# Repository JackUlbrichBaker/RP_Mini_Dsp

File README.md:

# DSP board

TODO:
- [ ] Create catchy name
- [x] Complete schematics
- [ ] review schematics
- [ ] revise schematics (if needed)
- [ ] Route board
- [ ] layout board

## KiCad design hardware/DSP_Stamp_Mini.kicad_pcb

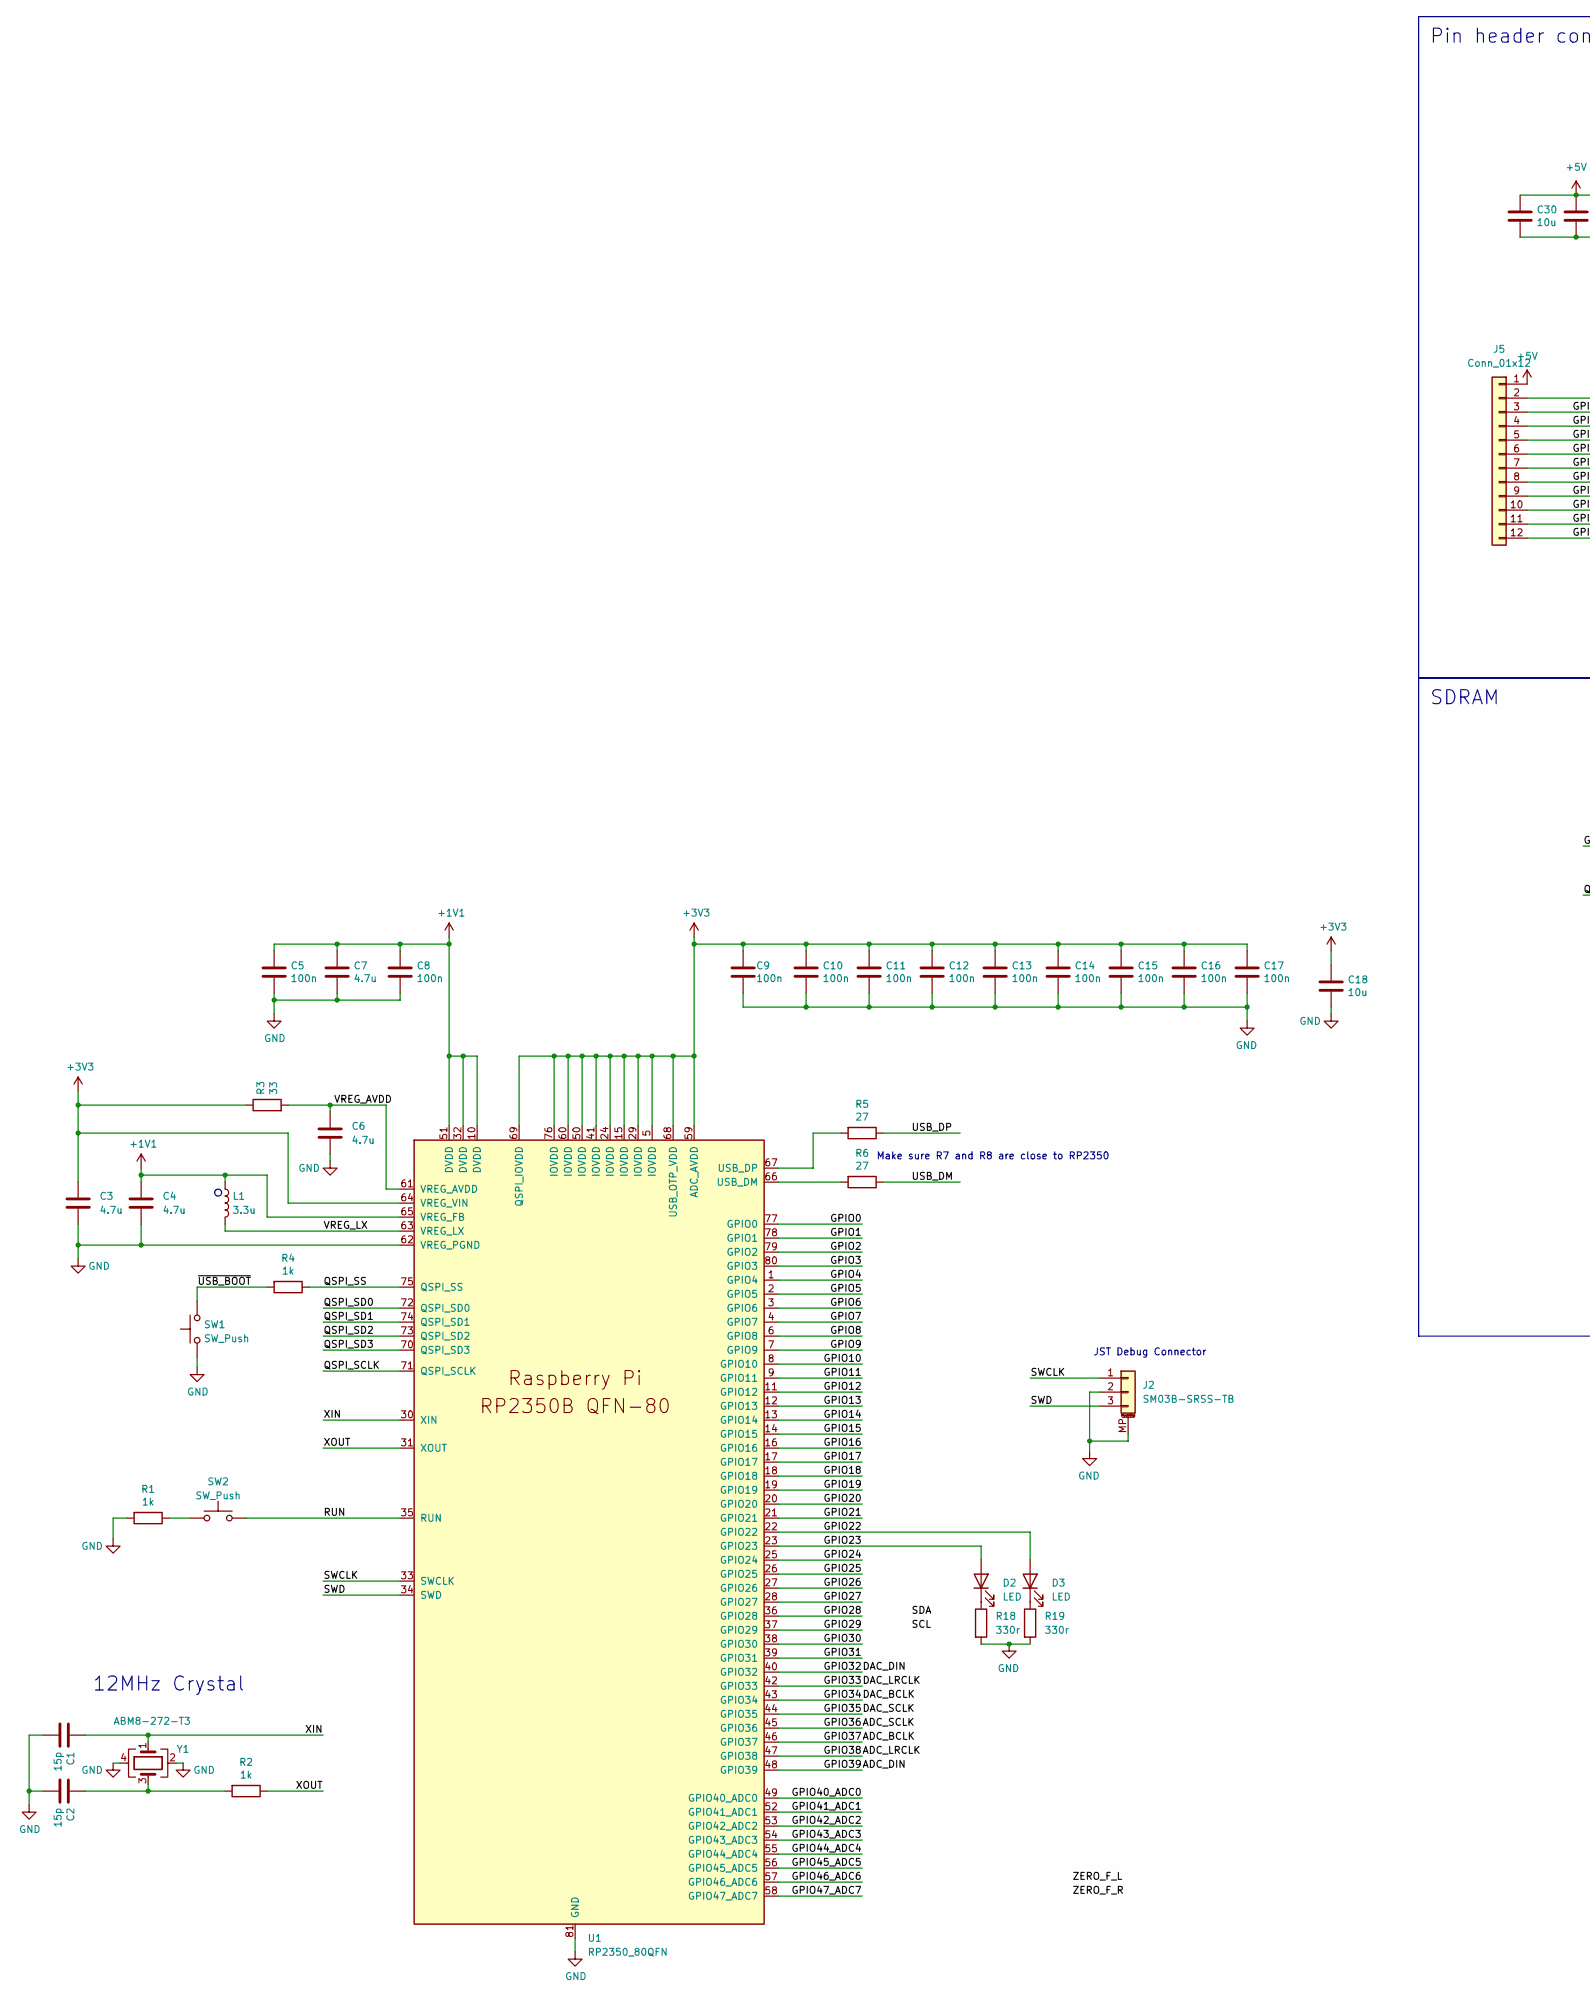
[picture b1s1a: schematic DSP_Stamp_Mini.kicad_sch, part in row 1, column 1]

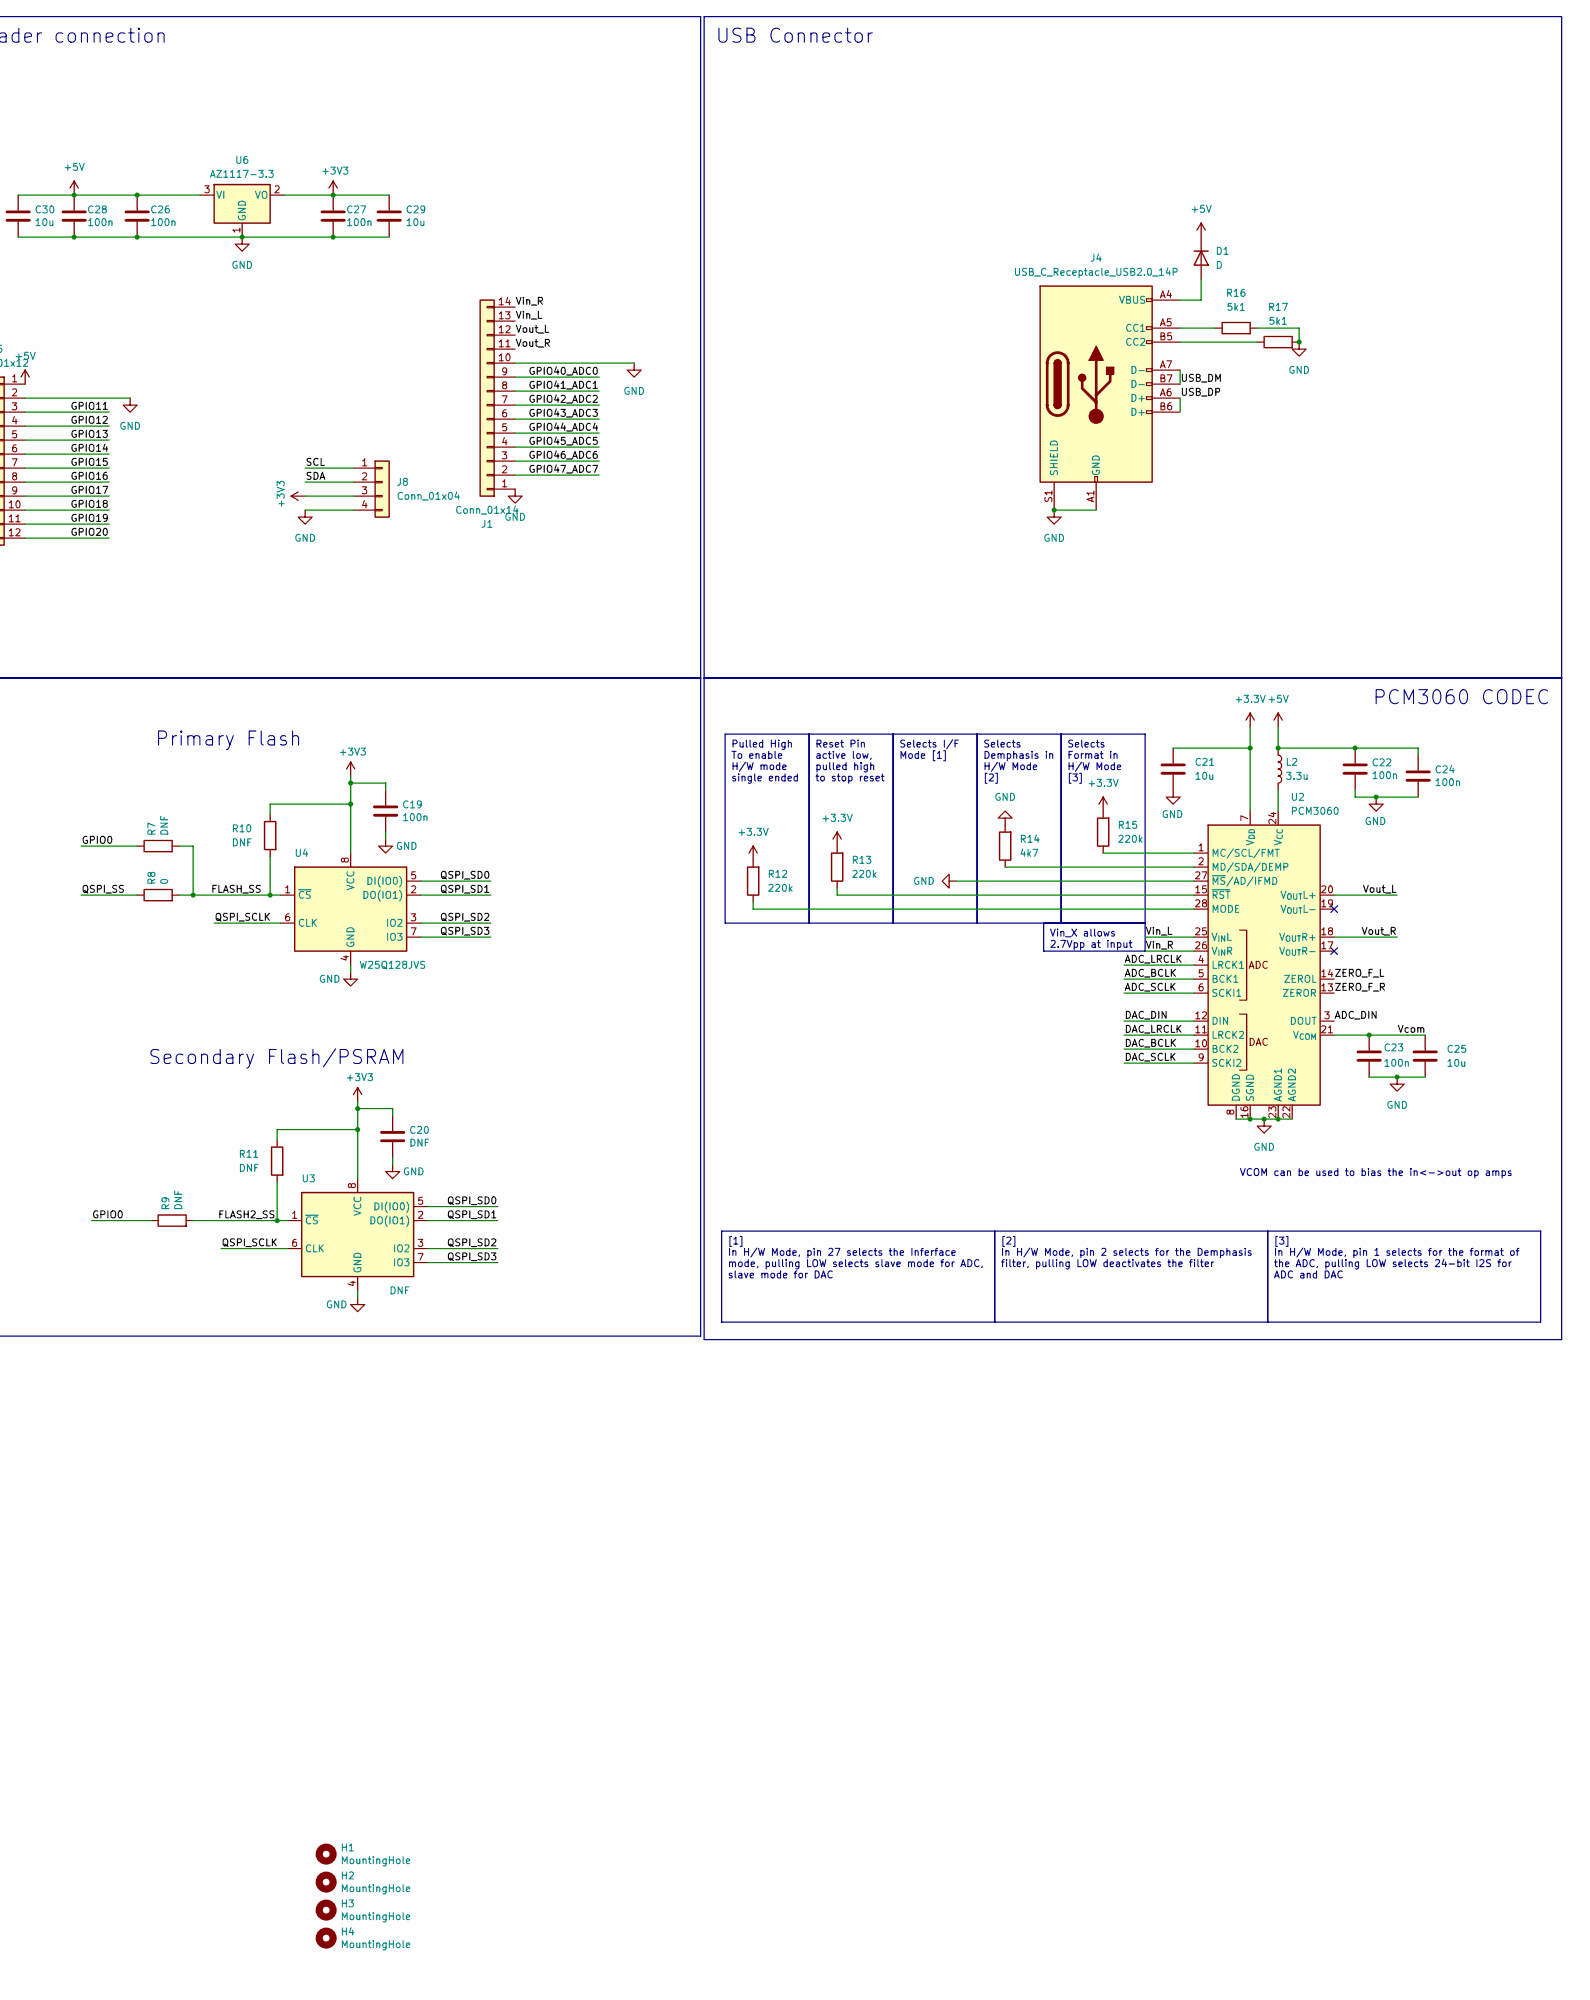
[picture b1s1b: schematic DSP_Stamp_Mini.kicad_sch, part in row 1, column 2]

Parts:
C1, C2: 15p; C_0603_1608Metric_Pad1.08x0.95mm_HandSolder
C3, C4, C6, C7: 4.7u; C_0603_1608Metric_Pad1.08x0.95mm_HandSolder
C5, C8, C9, C10, C11, C12, C13, C14, C15, C16, C17, C19, C22, C23, C24, C26, C27, C28: 100n; C_0603_1608Metric_Pad1.08x0.95mm_HandSolder
C18, C21, C25, C29, C30: 10u; C_0603_1608Metric_Pad1.08x0.95mm_HandSolder
C20: DNF; C_0603_1608Metric_Pad1.08x0.95mm_HandSolder
D1: D; D_0603_1608Metric
D2, D3: LED; LED_0603_1608Metric_Pad1.05x0.95mm_HandSolder
H1, H2, H3, H4: MountingHole; MountingHole_2.7mm_M2.5
J1: Conn_01x14; PinHeader_1x14_P2.54mm_Vertical
J2: SM03B-SRSS-TB; JST_SH_SM03B-SRSS-TB_1x03-1MP_P1.00mm_Horizontal
J4: USB_C_Receptacle_USB2.0_14P; USB_C_Receptacle_GCT_USB4105-xx-A_16P_TopMnt_Horizontal
J5: Conn_01x12; PinHeader_1x12_P2.54mm_Vertical
J8: Conn_01x04; JST_SH_SM04B-SRSS-TB_1x04-1MP_P1.00mm_Horizontal; Part Number 1-0401FBV0T
L1, L2: 3.3u; L_pol_2016
R1, R2, R4: 1k; R_0603_1608Metric_Pad0.98x0.95mm_HandSolder
R3: 33; R_0603_1608Metric_Pad0.98x0.95mm_HandSolder
R5, R6: 27; R_0603_1608Metric_Pad0.98x0.95mm_HandSolder
R7, R9, R10, R11: DNF; R_0603_1608Metric_Pad0.98x0.95mm_HandSolder
R8: 0; R_0603_1608Metric_Pad0.98x0.95mm_HandSolder
R12, R13, R15: 220k; R_0603_1608Metric_Pad0.98x0.95mm_HandSolder
R14: 4k7; R_0603_1608Metric_Pad0.98x0.95mm_HandSolder
R16, R17: 5k1; R_0603_1608Metric_Pad0.98x0.95mm_HandSolder
R18, R19: 330r; R_0603_1608Metric_Pad0.98x0.95mm_HandSolder
SW1, SW2: SW_Push; SW_Push_1P1T_NO_Vertical_Wuerth_434133025816
U1: RP2350_80QFN; RP2350-QFN-80-1EP_10x10_P0.4mm_EP3.4x3.4mm_ThermalVias
U2: PCM3060; TSSOP-28_4.4x9.7mm_P0.65mm
U3: DNF; SOIC-8_5.23x5.23mm_P1.27mm
U4: W25Q128JVS; SOIC-8_5.23x5.23mm_P1.27mm
U6: AZ1117-3.3; SOT-89-3
Y1: ABM8-272-T3; Crystal_SMD_3225-4Pin_3.2x2.5mm

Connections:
+1V1: C4.1, C5.1, C7.1, C8.1, L1.1, U1.10 (DVDD), U1.32 (DVDD), U1.51 (DVDD), U1.65 (VREG_FB)
+3.3V: C21.1, R12.2, R13.2, R15.2, U2.7 (V_{DD})
+3V3: C3.1, C9.1, C10.1, C11.1, C12.1, C13.1, C14.1, C15.1, C16.1, C17.1, C18.1, C19.1, C20.1, C27.1, C29.1, J8.3, R3.1, R10.1, R11.1, U1.5 (IOVDD), U1.15 (IOVDD), U1.24 (IOVDD), U1.29 (IOVDD), U1.41 (IOVDD), U1.50 (IOVDD), U1.59 (ADC_AVDD), U1.60 (IOVDD), U1.64 (VREG_VIN), U1.68 (USB_OTP_VDD), U1.69 (QSPI_IOVDD), U1.76 (IOVDD), U3.8 (VCC), U4.8 (VCC), U6.2 (VO)
+5V: C22.1, C24.1, C26.1, C28.1, C30.1, D1.1 (K), J5.1, L2.1, U6.3 (VI)
/ADC_BCLK: U1.46 (GPIO37), U2.5 (BCK1)
/ADC_DIN: U1.48 (GPIO39), U2.3 (DOUT)
/ADC_LRCLK: U1.47 (GPIO38), U2.4 (LRCK1)
/ADC_SCLK: U1.45 (GPIO36), U2.6 (SCKI1)
/DAC_BCLK: U1.43 (GPIO34), U2.10 (BCK2)
/DAC_DIN: U1.40 (GPIO32), U2.12 (DIN)
/DAC_LRCLK: U1.42 (GPIO33), U2.11 (LRCK2)
/DAC_SCLK: U1.44 (GPIO35), U2.9 (SCKI2)
/FLASH2_SS: R9.2, R11.2, U3.1 (~CS)
/FLASH_SS: R7.2, R8.2, R10.2, U4.1 (~CS)
/GPIO0: R7.1, R9.1, U1.77 (GPIO0)
/GPIO1: U1.78 (GPIO1)
/GPIO2: U1.79 (GPIO2)
/GPIO3: U1.80 (GPIO3)
/GPIO4: U1.1 (GPIO4)
/GPIO5: U1.2 (GPIO5)
/GPIO6: U1.3 (GPIO6)
/GPIO7: U1.4 (GPIO7)
/GPIO8: U1.6 (GPIO8)
/GPIO9: U1.7 (GPIO9)
/GPIO10: U1.8 (GPIO10)
/GPIO11: J5.3, U1.9 (GPIO11)
/GPIO12: J5.4, U1.11 (GPIO12)
/GPIO13: J5.5, U1.12 (GPIO13)
/GPIO14: J5.6, U1.13 (GPIO14)
/GPIO15: J5.7, U1.14 (GPIO15)
/GPIO16: J5.8, U1.16 (GPIO16)
/GPIO17: J5.9, U1.17 (GPIO17)
/GPIO18: J5.10, U1.18 (GPIO18)
/GPIO19: J5.11, U1.19 (GPIO19)
/GPIO20: J5.12, U1.20 (GPIO20)
/GPIO21: U1.21 (GPIO21)
/GPIO22: D3.2 (A), U1.22 (GPIO22)
/GPIO23: D2.2 (A), U1.23 (GPIO23)
/GPIO24: U1.25 (GPIO24)
/GPIO25: U1.26 (GPIO25)
/GPIO26: U1.27 (GPIO26)
/GPIO27: U1.28 (GPIO27)
/GPIO28: U1.36 (GPIO28)
/GPIO29: U1.37 (GPIO29)
/GPIO30: U1.38 (GPIO30)
/GPIO31: U1.39 (GPIO31)
/GPIO40_ADC0: J1.9, U1.49 (GPIO40_ADC0)
/GPIO41_ADC1: J1.8, U1.52 (GPIO41_ADC1)
/GPIO42_ADC2: J1.7, U1.53 (GPIO42_ADC2)
/GPIO43_ADC3: J1.6, U1.54 (GPIO43_ADC3)
/GPIO44_ADC4: J1.5, U1.55 (GPIO44_ADC4)
/GPIO45_ADC5: J1.4, U1.56 (GPIO45_ADC5)
/GPIO46_ADC6: J1.3, U1.57 (GPIO46_ADC6)
/GPIO47_ADC7: J1.2, U1.58 (GPIO47_ADC7)
/QSPI_SCLK: U1.71 (QSPI_SCLK), U3.6 (CLK), U4.6 (CLK)
/QSPI_SD0: U1.72 (QSPI_SD0), U3.5 (DI(IO0)), U4.5 (DI(IO0))
/QSPI_SD1: U1.74 (QSPI_SD1), U3.2 (DO(IO1)), U4.2 (DO(IO1))
/QSPI_SD2: U1.73 (QSPI_SD2), U3.3 (IO2), U4.3 (IO2)
/QSPI_SD3: U1.70 (QSPI_SD3), U3.7 (IO3), U4.7 (IO3)
/QSPI_SS: R4.1, R8.1, U1.75 (QSPI_SS)
/RUN: SW2.2, U1.35 (RUN)
/SCL: J8.1
/SDA: J8.2
/SWCLK: J2.1, U1.33 (SWCLK)
/SWD: J2.3, U1.34 (SWD)
/USB_DM: J4.A7 (D-), J4.B7 (D-), R6.1
/USB_DP: J4.A6 (D+), J4.B6 (D+), R5.1
/VREG_AVDD: C6.1, R3.2, U1.61 (VREG_AVDD)
/VREG_LX: L1.2, U1.63 (VREG_LX)
/Vcom: C23.1, C25.1, U2.21 (V_{COM})
/Vin_L: J1.13, U2.25 (V_{IN}L)
/Vin_R: J1.14, U2.26 (V_{IN}R)
/Vout_L: J1.12, U2.20 (V_{OUT}L+)
/Vout_R: J1.11, U2.18 (V_{OUT}R+)
/XIN: C1.1, U1.30 (XIN), Y1.1
/XOUT: R2.1, U1.31 (XOUT)
/ZERO_F_L: U2.14 (ZEROL)
/ZERO_F_R: U2.13 (ZEROR)
/~USB_BOOT: R4.2, SW1.2
GND: C1.2, C2.2, C3.2, C4.2, C5.2, C6.2, C7.2, C8.2, C9.2, C10.2, C11.2, C12.2, C13.2, C14.2, C15.2, C16.2, C17.2, C18.2, C19.2, C20.2, C21.2, C22.2, C23.2, C24.2, C25.2, C26.2, C27.2, C28.2, C29.2, C30.2, J1.1, J1.10, J2.2, J2.MP (MountPin), J4.A1 (GND), J4.A12 (GND), J4.B1 (GND), J4.B12 (GND), J4.S1 (SHIELD), J5.2, J8.4, R1.2, R14.2, R16.2, R17.2, R18.2, R19.2, SW1.1, U1.62 (VREG_PGND), U1.81 (GND), U2.8 (DGND), U2.16 (SGND), U2.22 (AGND2), U2.23 (AGND1), U2.27 (~MS/AD/IFMD), U3.4 (GND), U4.4 (GND), U6.1 (GND), Y1.2, Y1.4
unnamed: C2.1, R2.2, Y1.3
unnamed: D1.2 (A), J4.A4 (VBUS), J4.A9 (VBUS), J4.B4 (VBUS), J4.B9 (VBUS)
unnamed: D2.1 (K), R18.1
unnamed: D3.1 (K), R19.1
unnamed: J4.A5 (CC1), R16.1
unnamed: J4.B5 (CC2), R17.1
unnamed: R1.1, SW2.1
unnamed: R6.2, U1.66 (USB_DM)
unnamed: R5.2, U1.67 (USB_DP)
unnamed: R15.1, U2.1 (MC/SCL/FMT)
unnamed: R14.1, U2.2 (MD/SDA/DEMP)
unnamed: R12.1, U2.28 (MODE)
unnamed: L2.2, U2.24 (V_{CC})
unnamed: R13.1, U2.15 (~RST)

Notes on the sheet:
Vin_X allows 2.7Vpp at input
Selects Format in H/W Mode [3]
[3] In H/W Mode, pin 1 selects for the format of the ADC, pulling LOW selects 24-bit I2S for ADC and DAC
Pin header connection
PCM3060 CODEC
[1] In H/W Mode, pin 27 selects the Inferface mode, pulling LOW selects slave mode for ADC, slave mode for DAC
Selects I/F Mode [1]
Selects Demphasis in H/W Mode [2]
Reset Pin active low, pulled high to stop reset
USB Connector
Pulled High To enable H/W mode single ended
[2] In H/W Mode, pin 2 selects for the Demphasis filter, pulling LOW deactivates the filter
SDRAM
JST Debug Connector
VCOM can be used to bias the in<->out op amps
12MHz Crystal
Make sure R7 and R8 are close to RP2350
Primary Flash
Secondary Flash/PSRAM

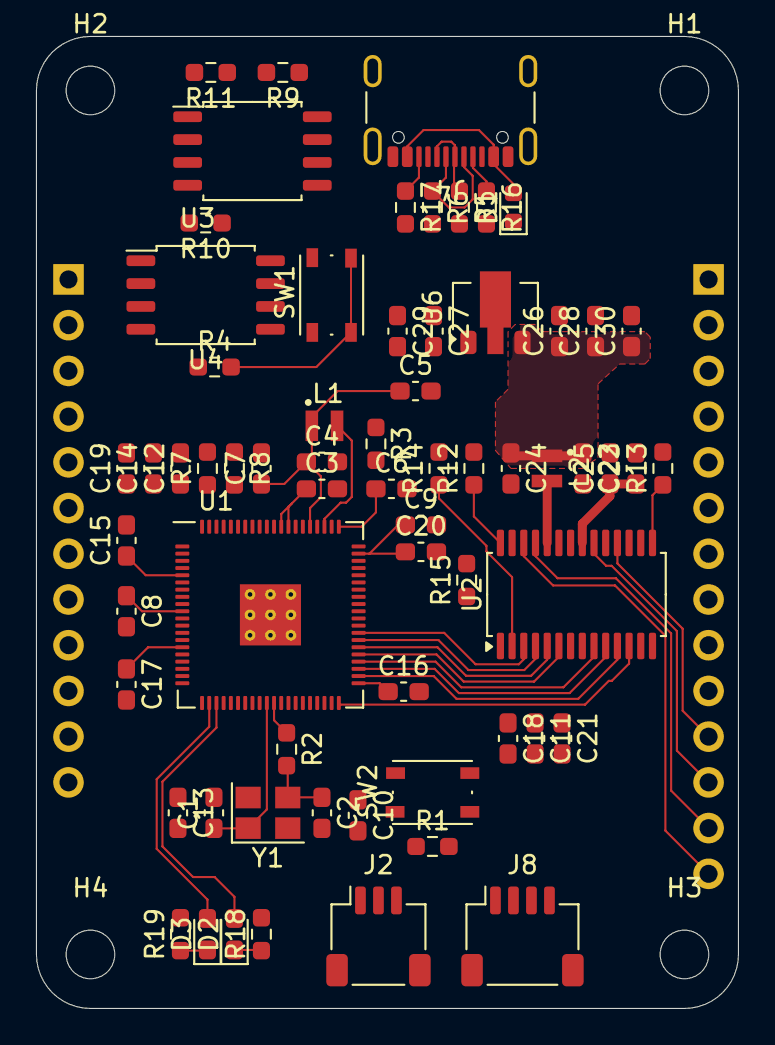
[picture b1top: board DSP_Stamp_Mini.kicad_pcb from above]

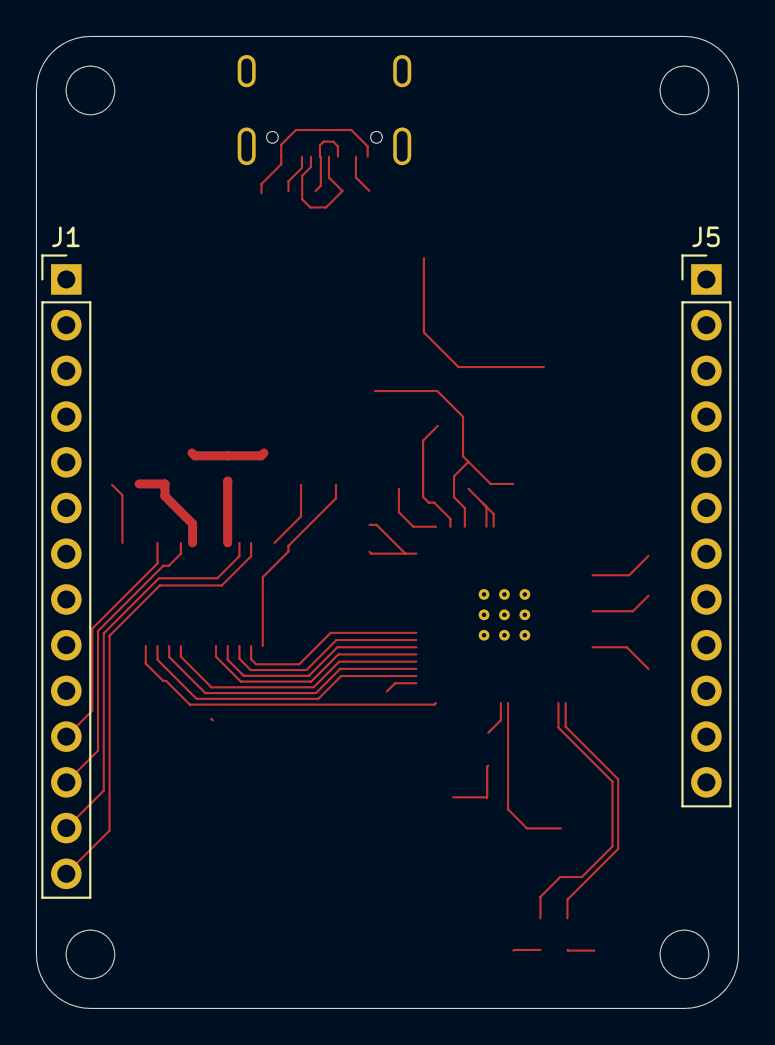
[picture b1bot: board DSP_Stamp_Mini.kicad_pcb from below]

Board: 2 copper layers, 39.0 x 54.0 mm, 71 parts (2 on the bottom side), 71 nets.

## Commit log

2024-09-05 inital dump of files
2024-09-05 small schematic changes for readability
2024-09-06 switched pin headers to SMD, changed board shape and redid layout
2024-09-17 repo cleanup
2024-09-18 change PCMxxx routing, partially route
